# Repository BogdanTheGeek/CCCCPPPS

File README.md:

# Cheap Crappy Constant Current Portable Programmable Power Supply 

`CCCCPPPS` is a DIY Programmable Buck/Boost Power Supply, designed with the goal
of being cheap, crappy, but very useful!  

# Usage
## Web UI
https://bogdanthegeek.github.io/CCCCPPPS/software/webui/index.html
## Debug Interface:
This interface is enabled by default when building the firmware. Use `minichlink`
to issue commands listed below

## Commands
> [!NOTE]
> Need to improve the command list and handler

- `0` to turn the supply off
- `1-9` to set the target Voltage/Current in multiples of 1000mV/100mA
- `c` to switch to Constant Current Mode 
- `v` to switch to Constant Voltage Mode
- `+` to increase the target Voltage/Current depending on mode, in 50mV/25mA increments
- `-` to decrease the target Voltage/Current depending on mode, in 50mV/25mA increments
- ~~Konami code makes the unit self distruct.~~ Removed due to misuse.

# Build
```sh
export CH32V003FUN="path/to/ch32v003fun"
make
```

----
(c) 2024  
[Bogdan Ionescu](https://github.com/BogdanTheGeek)  
[ADBeta](https://github.com/ADBeta)

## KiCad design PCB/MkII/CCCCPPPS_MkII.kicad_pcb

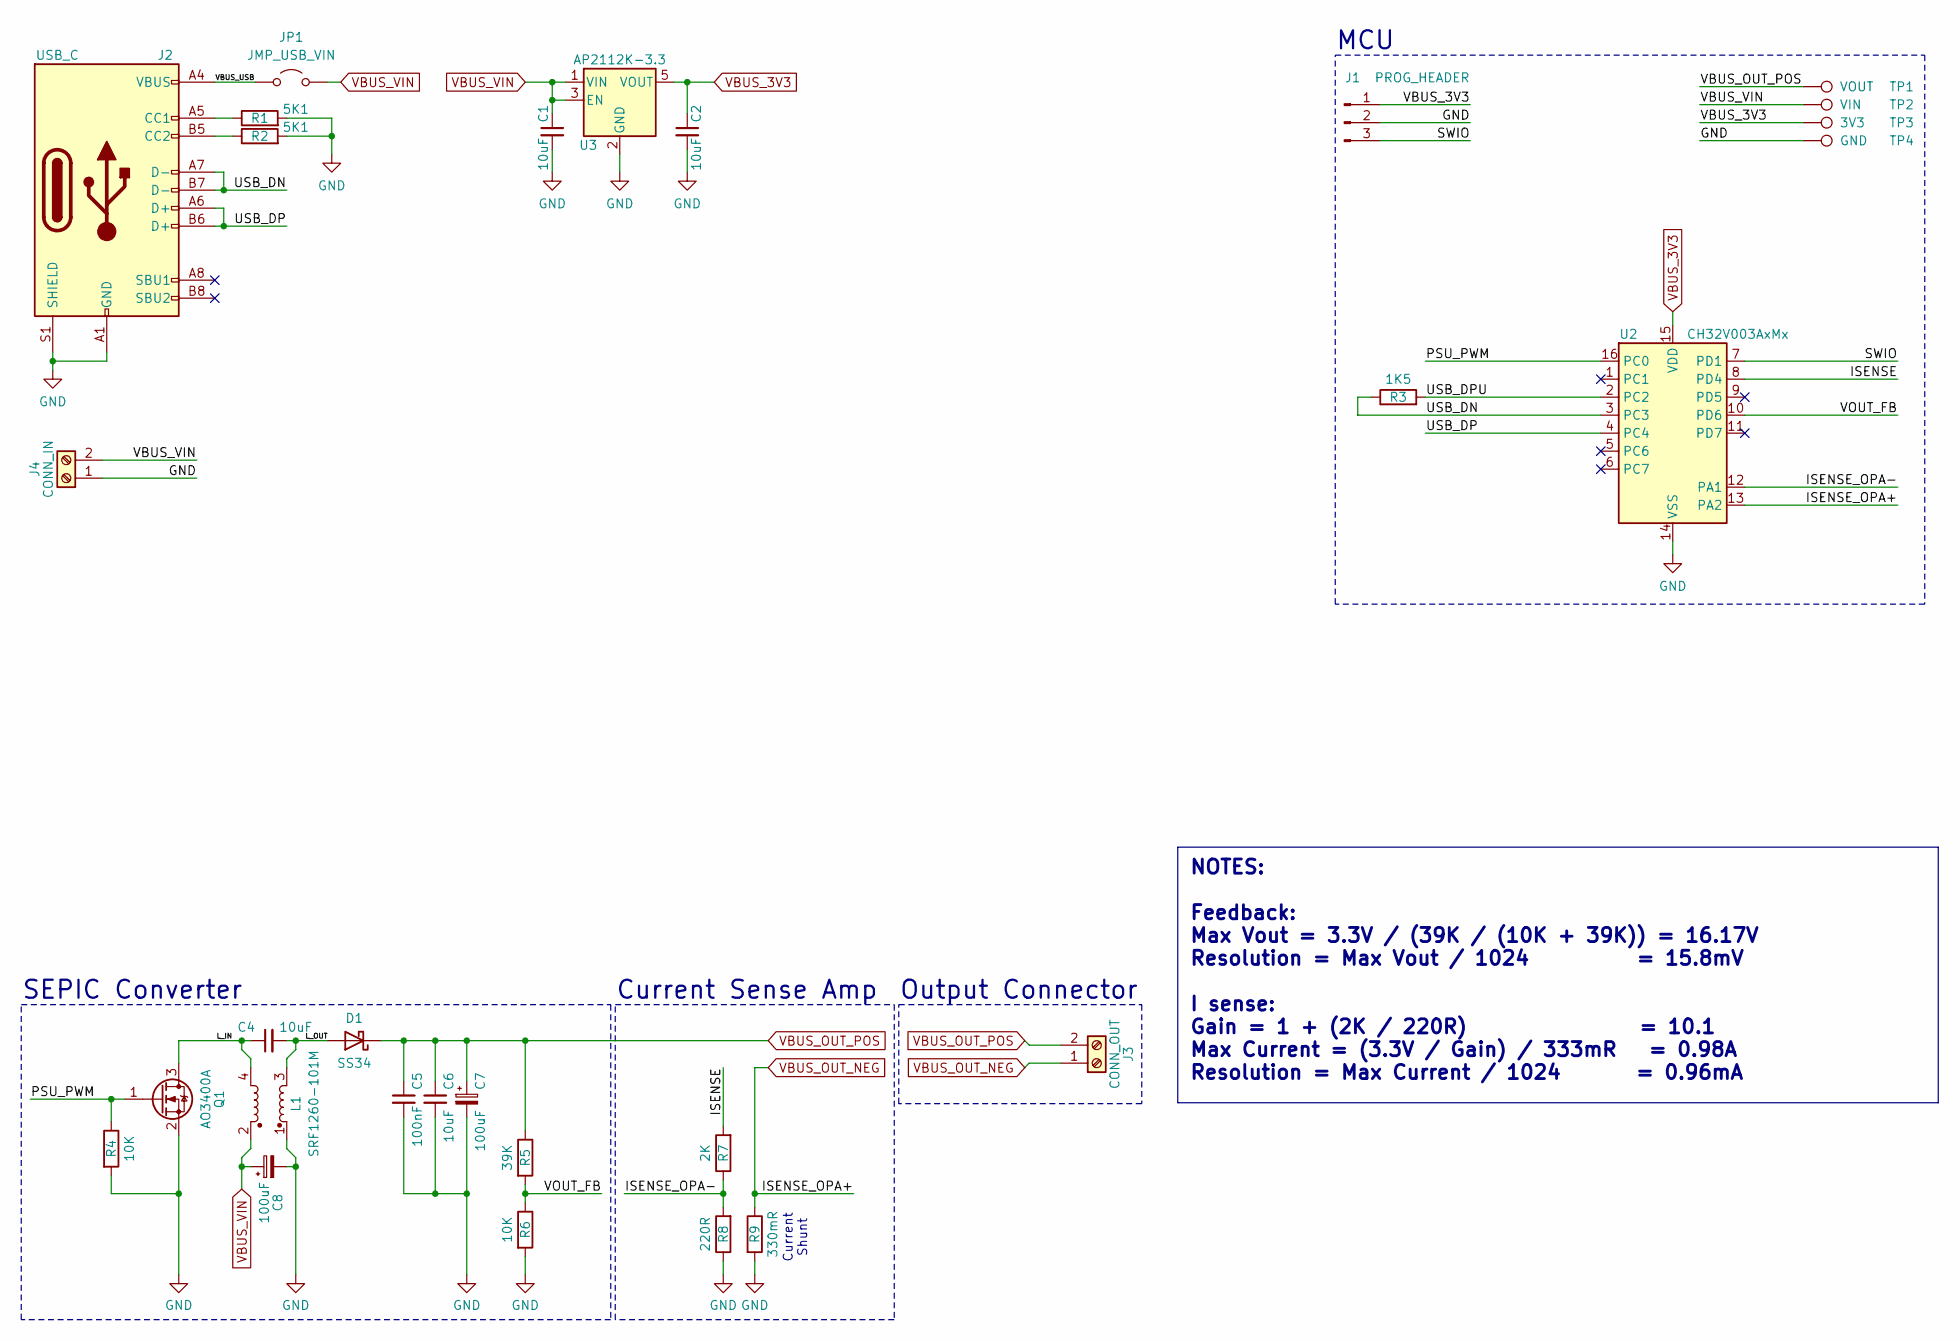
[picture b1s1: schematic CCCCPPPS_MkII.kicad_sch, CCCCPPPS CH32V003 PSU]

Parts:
C1, C2, C4, C6: 10uF; C_0805_2012Metric
C5: 100nF; C_0805_2012Metric
C7, C8: 100uF; CP_Elec_6.3x5.2
D1: SS34; D_SMA
J1: PROG_HEADER; PinHeader_1x03_P2.54mm_Vertical
J2: USB_C; USB_C_Receptacle_G-Switch_GT-USB-7010ASV
J3: CONN_OUT; PCB_Terminal_Block_2-P3.5
J4: CONN_IN; PCB_Terminal_Block_2-P3.5
JP1: JMP_USB_VIN; SolderJumper-2_P1.3mm_Open_RoundedPad1.0x1.5mm
L1: SRF1260-101M; L_Bourns_SRF1260
Q1: AO3400A; SOT-23
R1, R2: 5K1; R_0805_2012Metric
R3: 1K5; R_0805_2012Metric
R4, R6: 10K; R_0805_2012Metric
R5: 39K; R_0805_2012Metric
R7: 2K; R_0805_2012Metric
R8: 220R; R_0805_2012Metric
R9: 330mR; R_2512_6332Metric_Pad1.40x3.35mm_HandSolder
TP1: VOUT; TestPoint_Pad_D1.5mm
TP2: VIN; TestPoint_Pad_D1.5mm
TP3: 3V3; TestPoint_Pad_D1.5mm
TP4: GND; TestPoint_Pad_D1.5mm
U2: CH32V003AxMx; SOP-16_3.9x9.9mm_P1.27mm
U3: AP2112K-3.3; SOT-23-5

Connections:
/ISENSE: R7.2, U2.8 (PD4)
/ISENSE_OPA-: R7.1, R8.2, U2.12 (PA1)
/L_IN: C4.1, L1.4, Q1.3 (D)
/L_OUT: C4.2, D1.2 (A), L1.3
/PSU_PWM: Q1.1 (G), R4.1, U2.16 (PC0)
/SWIO: J1.3, U2.7 (PD1)
/USB_DN: J2.A7 (D-), J2.B7 (D-), R3.1, U2.3 (PC3)
/USB_DP: J2.A6 (D+), J2.B6 (D+), U2.4 (PC4)
/USB_DPU: R3.2, U2.2 (PC2)
/VBUS_USB: J2.A4 (VBUS), J2.A9 (VBUS), J2.B4 (VBUS), J2.B9 (VBUS), JP1.1 (A)
/VOUT_FB: R5.2, R6.1, U2.10 (PD6)
GND: C1.2, C2.2, C5.2, C6.2, C7.2, C8.2, J1.2, J2.A1 (GND), J2.A12 (GND), J2.B1 (GND), J2.B12 (GND), J2.S1 (SHIELD), J4.1, L1.1, Q1.2 (S), R1.2, R2.2, R4.2, R6.2, R8.1, R9.2, TP4.1, U2.14 (VSS), U3.2 (GND)
unnamed: J2.A5 (CC1), R1.1
unnamed: J2.B5 (CC2), R2.1
VBUS_3V3: C2.1, J1.1, TP3.1, U2.15 (VDD), U3.5 (VOUT)
VBUS_OUT_NEG: J3.1, R9.1, U2.13 (PA2)
VBUS_OUT_POS: C5.1, C6.1, C7.1, D1.1 (K), J3.2, R5.1, TP1.1
VBUS_VIN: C1.1, C8.1, J4.2, JP1.2 (B), L1.2, TP2.1, U3.1 (VIN), U3.3 (EN)

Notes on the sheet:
NOTES: Feedback: Max Vout = 3.3V / (39K / (10K + 39K)) = 16.17V Resolution = Max Vout / 1024 = 15.8mV I sense: Gain = 1 + (2K / 220R) = 10.1 Max Current = (3.3V / Gain) / 333mR = 0.98A Resolution = Max Current / 1024 = 0.96mA
MCU
Output Connector
Current Shunt
SEPIC Converter
Current Sense Amp

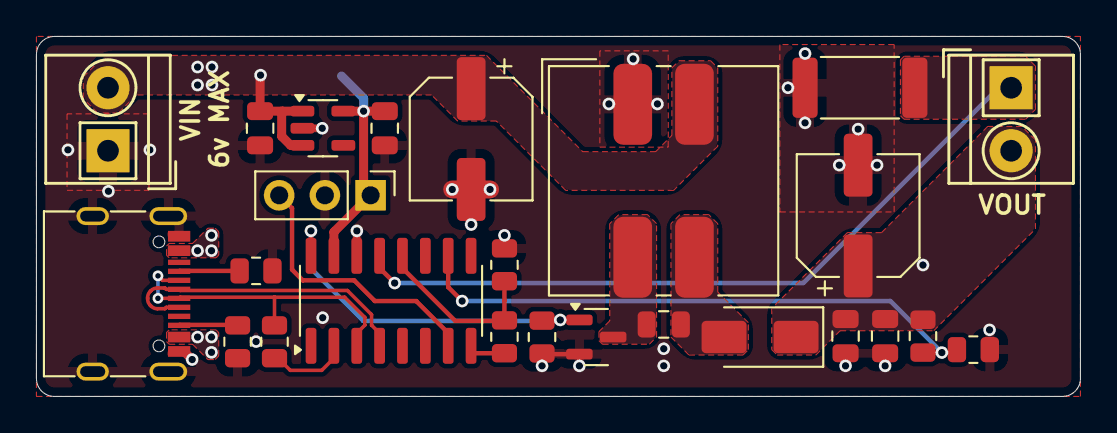
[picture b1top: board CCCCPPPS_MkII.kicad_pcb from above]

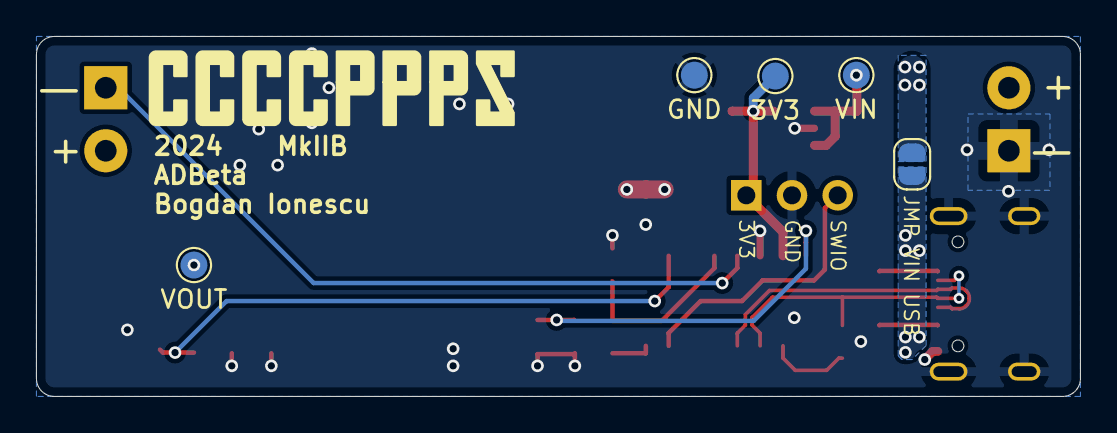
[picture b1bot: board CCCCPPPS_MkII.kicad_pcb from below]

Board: 2 copper layers, 58.0 x 20.0 mm, 30 parts (5 on the bottom side), 18 nets.

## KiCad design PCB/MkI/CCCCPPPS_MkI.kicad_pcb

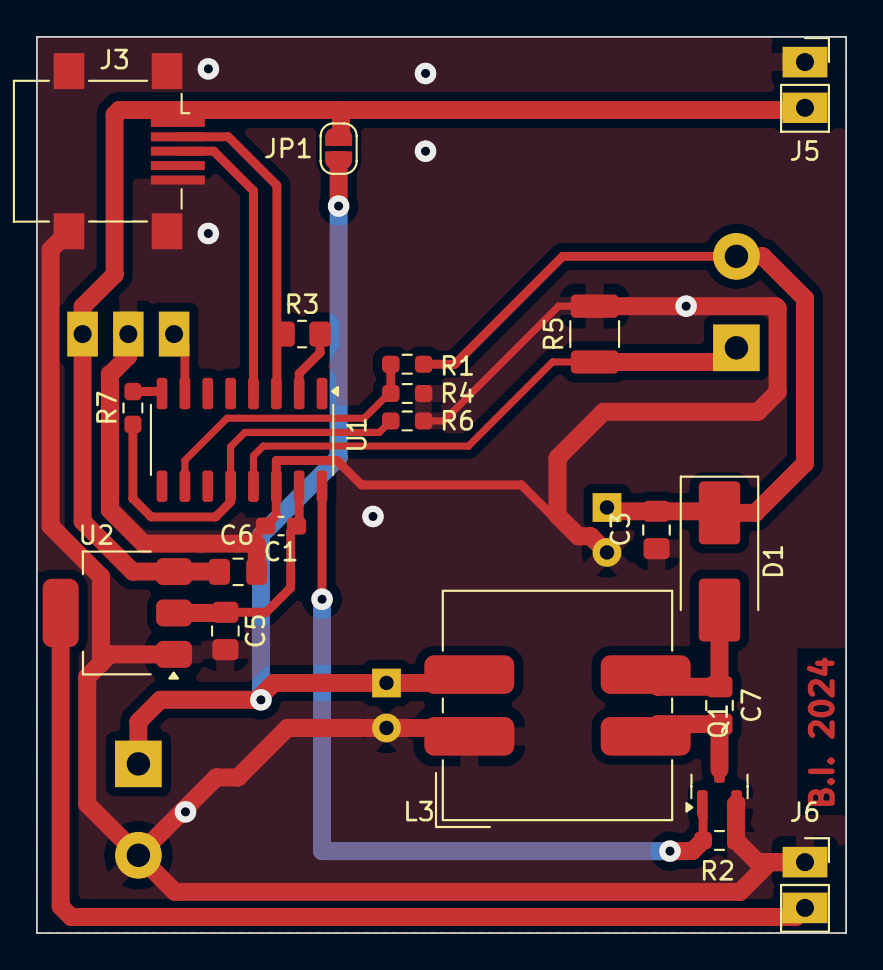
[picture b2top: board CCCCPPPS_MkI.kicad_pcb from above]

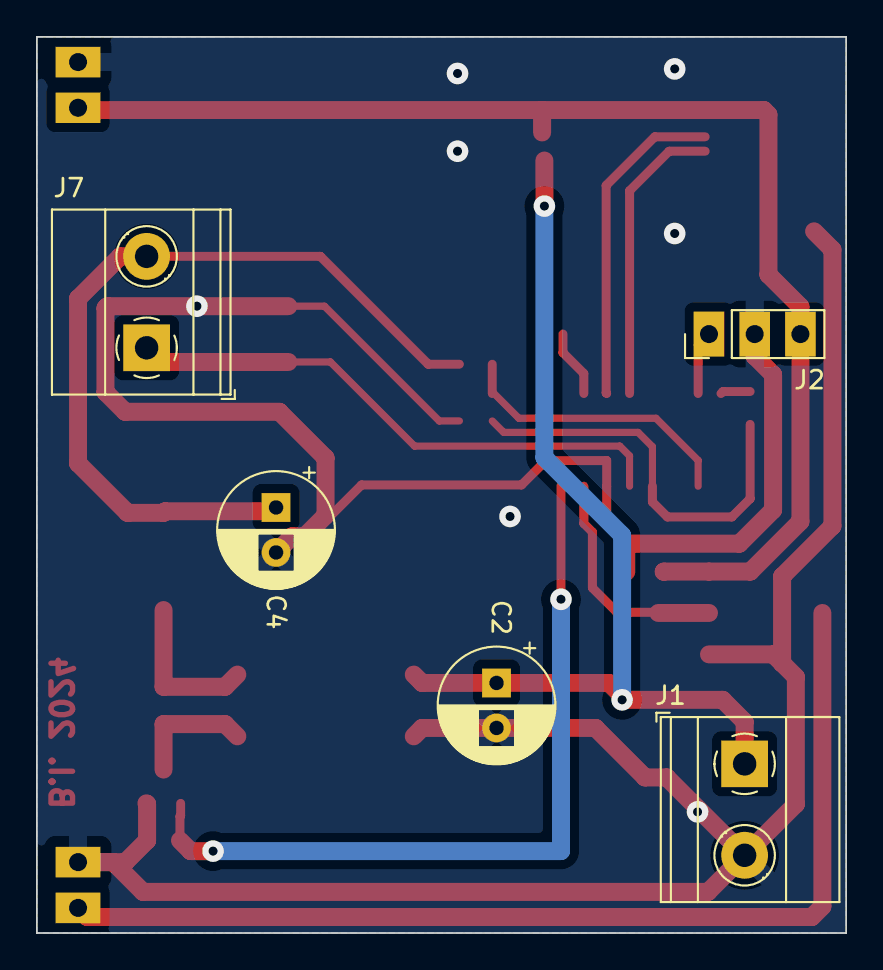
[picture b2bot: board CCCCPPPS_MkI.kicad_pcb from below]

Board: 2 copper layers, 45.0 x 49.8 mm, 26 parts (5 on the bottom side), 16 nets.

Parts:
C1: 0.1uF; C_0603_1608Metric_Pad1.08x0.95mm_HandSolder
C2: 100uF; CP_Radial_D6.3mm_P2.50mm
C3, C6, C7: 10uF; C_0805_2012Metric_Pad1.18x1.45mm_HandSolder
C4: 100uF 25V; CP_Radial_D6.3mm_P2.50mm
C5: 1uF; C_0805_2012Metric_Pad1.18x1.45mm_HandSolder
D1: B2100-13-F; D_SMB_Handsoldering
J1, J7: Screw_Terminal_01x02; TerminalBlock_Phoenix_MKDS-1,5-2-5.08_1x02_P5.08mm_Horizont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
J2: PROG; PinHeader_1x03_P2.54mm_Vertical
J3: USB_B_Mini; USB_Mini-B_Lumberg_2486_01_Horizontal
J5, J6: Conn_01x02; PinSocket_1x02_P2.54mm_Vertical
JP1: SolderJumper_2_Open; SolderJumper-2_P1.3mm_Open_RoundedPad1.0x1.5mm
L3: SRF1260-101M; L_Bourns_SRF1260
Q1: AO3400A; SOT-23
R1: 39k; R_0603_1608Metric_Pad0.98x0.95mm_HandSolder
R2, R4: 10k; R_0603_1608Metric_Pad0.98x0.95mm_HandSolder
R3: 1K5; R_0805_2012Metric_Pad1.20x1.40mm_HandSolder
R5: 333mΩ; R_1210_3225Metric_Pad1.30x2.65mm_HandSolder
R6: 220R; R_0603_1608Metric_Pad0.98x0.95mm_HandSolder
R7: 2k; R_0603_1608Metric_Pad0.98x0.95mm_HandSolder
U1: CH32V003A4M6; SO-16_3.9x9.9mm_P1.27mm
U2: AZ1117-3.3; SOT-223-3_TabPin2

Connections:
+3V3: C1.1, C5.1, J6.2, U1.15 (VDD), U2.2 (VO)
+5V: C6.1, J2.3, J3.1 (VBUS), J5.2, JP1.2 (B), U2.3 (VI)
/VOUT+: C3.1, C4.1, D1.1 (K), J7.2, R1.1
GND: C1.2, C2.2, C3.2, C4.2, C5.2, C6.2, J1.2, J2.2, J3.5 (GND), J3.6 (Shield), J5.1, J6.1, L3.1, Q1.2 (S), R2.2, R4.2, R5.2, R6.1, U1.14 (vss), U2.1 (GND)
unnamed: C7.2, D1.2 (A), L3.3
unnamed: C7.1, L3.4, Q1.3 (D)
PA1: R6.2, R7.1, U1.12 (PA1_A1_T1CH2_OSCI)
PA2: J7.1, R5.1, U1.13 (PA2_A0_T1CH2N_OSCO)
PC0: Q1.1 (G), R2.1, U1.16 (PC0_T2CH3)
PC2: R3.1, U1.2 (PC2_SCL)
PC3: J3.2 (D-), R3.2, U1.3 (PC3)
PC4: J3.3 (D+), U1.4 (PC4_A2_T1CH4)
PD4: R7.2, U1.8 (PD4_A7_T2AETR2)
PD6: R1.2, R4.1, U1.10 (PD6_A6_UART_RX)
SWIO: J2.1, U1.7 (SWIO&PD1_T1CH3N)
VPP: C2.1, J1.1, JP1.1 (A), L3.2

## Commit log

2024-10-29 init
2024-10-29 readme: move to root
2024-10-29 main: comments and cleanup
2024-11-02 main: boost: switch to limit PID control
2024-11-03 main: ui: usb: implement web ui and usb coms (debug commands disabled)
2024-11-05 webui: boost: usb: move to plotly.js, move state into boost module, optimise settings
2024-11-05 LICENCE
2024-11-06 webui: add jsdoc types and fix indent width
2024-11-07 firmware: add bootloader and small speed ups
2024-11-07 webui: cleanup and optmisations, link web flasher
2024-11-14 MkII Cleanup
2024-11-14 Added MkII PCB
2024-11-29 firmware: webui: fix windows
2024-12-01 save settings to NVS
2024-12-10 MkII PCB and Updated README
2024-12-10 Apply suggestions from code review
2024-12-11 Fixed MkII USB and Polarity issues. MkIIB
2024-12-11 Updated PCB Images
2024-12-11 Fixed Polarity Marking, for real this time :)
